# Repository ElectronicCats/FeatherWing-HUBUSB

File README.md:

# WingHub

## License
Electronic Cats invests time and resources providing this open source design, please support Electronic Cats and open-source hardware by purchasing products from Electronic Cats!

Designed by Electronic Cats.

Firmware released under an GNU AGPL v3.0 license. See the LICENSE file for more information.

Hardware released under an CERN Open Hardware Licence v1.2. See the LICENSE_HARDWARE file for more information.

Electronic Cats is a registered trademark, please do not use if you sell these PCBs.

Jun 2020

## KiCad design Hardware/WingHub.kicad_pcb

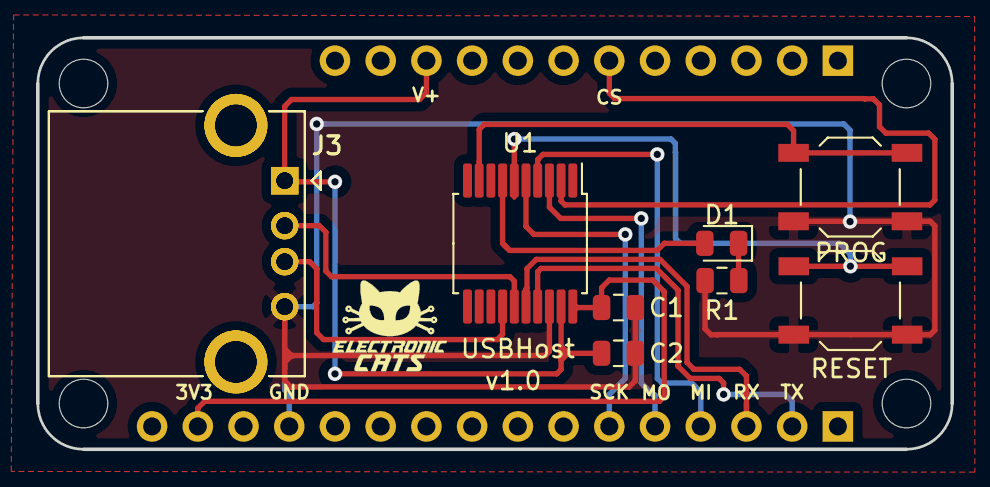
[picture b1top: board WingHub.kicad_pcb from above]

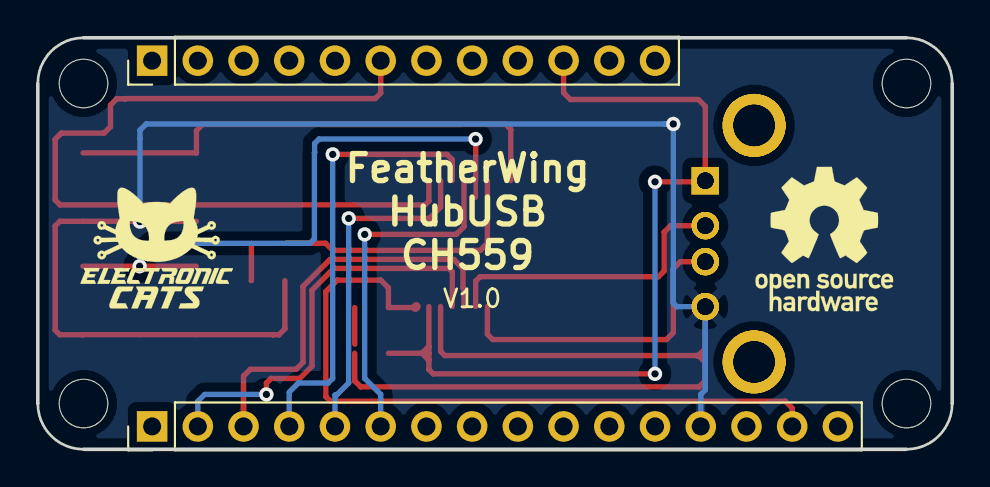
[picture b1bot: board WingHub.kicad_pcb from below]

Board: 2 copper layers, 50.8 x 22.9 mm, 11 parts (2 on the bottom side), 16 nets.

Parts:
C1: 0.1uF; C_0805_2012Metric
C2: 3.3uF; C_0805_2012Metric
D1: LED; LED_0805_2012Metric
J1: feather long; PinHeader_1x16_P2.54mm_Vertical
J2: feather short; PinHeader_1x12_P2.54mm_Vertical
J3, J3#2: USB_A; USB_A_CONNFLY_DS1095-WNR0
PROG: DOWNLOADER; SW_SPST_TL3342
R1: 1K; R_0805_2012Metric
RESET: RESET; SW_SPST_TL3342
U1: CH559T; SSOP-20_5.3x7.2mm_P0.65mm

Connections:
+3V3: C1.1, J1.15, U1.20
/CS: J2.6, U1.2
/D+: J3.3, J3#2.3, U1.14
/D-: J3.2, J3#2.2, U1.15
/LED: D1.2, U1.7
/MISO: J1.4, U1.4
/MOSI: J1.5, U1.3
/PROG: PROG.1, U1.9
/RST: RESET.1, U1.6
/RX: J1.3, U1.16
/SCK: J1.6, U1.5
/TX: J1.2, U1.17
GND: C1.2, C2.2, J1.13, J3.4, J3#2.4, PROG.2, R1.2, RESET.2, U1.18
unnamed: D1.1, R1.1
unnamed: J3.5, J3#2.5
VBUS: C2.1, J2.10, J3.1, J3#2.1, U1.19

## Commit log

2020-05-22 Init schematic
2020-05-22 Update Wings format
2020-05-23 TEST Gitkraken
2020-05-23 Update schematic
2020-05-27 CH559L Updated
2020-05-28 Pre-routed HUSUSB PCB
2020-05-29 Routed and copper-zone-filled HUSUSB_PCB
2020-05-29 add SPI and LED serial data
2020-05-29 add logos and LED serial data
2020-05-29 Added electronic devices are routed.
2020-05-30 Silk screen tags moved
2020-05-30 add HubUSB 3D Model
2020-05-30 layers ok
2020-06-01 Tracers are updated
2020-06-01 add model USB 3D
2020-06-01 change tx and rx
2020-06-01 fix labels pinout
2020-06-01 Tx and Rx routes exchanged.
2020-06-01 labels buttons
2020-06-02 WingHubBom.ods created with plugin.
2020-06-03 Firmware folder and WingHub.csv (BOM) created.
2020-06-17 Blinked D1 example and hardware change list added.
2020-06-18 Greetings added
2020-06-18 Greetings fixed
2020-06-22 Hardware change list upgraded.
2020-06-22 Deleted archives.
2020-06-22 Hardware changes added
